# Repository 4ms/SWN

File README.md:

# Spherical Wavetable Navigator

Firmware for the Spherical Wavetable Navigator, a Eurorack-format module from 4ms Company.

## Setting up the gcc-arm toolchain
You need to install the GCC ARM toolchain.
This project is known to compile with arm-none-eabi-gcc version 8.2.1 (8-2019q4) and 7.3.1 (7-2018q2).

If you're new to embedded development and not comfortable on the command line, you may wish to install an IDE. ST has an official IDE based on Eclipse called [STM32CubeIDE](https://www.st.com/en/development-tools/stm32cubeide.html). Or you can roll-your-own Eclipse using [GCC ARM with Eclipse](https://gnu-mcu-eclipse.github.io/). There are also commerical software packages which can be easily found by searching.

Another option is to use a fully-featured text editor such as VSCode or Sublime Text. You can configure these to run commands to compile and flash/program your project onto your SWN, too. There are ARM debugging extensions available, too. On the other hand, if you're happiest using the command line and prefer to write code with vim, emacs, etc, you can also do everything without having to lift your hand from the keyboard except to twiddle knobs on the SWN.

### Using the Virtual Machine ###

4ms has a virtual machine that provides a consistant development environment for compiling. Check out this project and follow the instructions in its README: [4ms-dev-env](https://github.com/4ms/4ms-dev-env). The SWN repo comes pre-cloned when you start this virtual machine.

First, follow the instructions on [vagrant's site](https://www.vagrantup.com/intro/getting-started) to install vagrant and VirtualBox.

Then, building the SWN project is as simple as this:

```
git clone https://github.com/4ms/4ms-dev-env.git
cd 4ms-dev-env
vagrant up
vagrant ssh
cd SWN
make
```

At present, the 4ms-dev-env is only setup to compile, not to flash (program), or debug.
If you decide to use the virtual machine to compile, you'll still need to use your local system to program the compiled code onto SWN. Skip down to the **Programmer** section.

### Mac OSX using Brew ###

For Mac OSX, you can use brew to install the gcc-arm toolchain.
First, install brew if you haven't already:
```
ruby -e "$(curl -fsSL https://raw.githubusercontent.com/Homebrew/install/master/install)"
```

Then, install the gcc-arm toolchain v7.3.1:

```
brew tap nitsky/stm32
brew install arm-none-eabi-gcc
```

Continue below to **Clone the Projects**

Alternatively, you can follow the _Linux orMac OSX_ instructions below to get v8.2.1.

### Linux or Mac OSX ###

For Linux or Mac OSX, download GNU ARM Embedded Toolchain version 8-2018-q4-major from [Launchpad](https://launchpad.net/gcc-arm-embedded/+download).

Direct links: [Mac OSX gcc-arm 8.2.1](https://developer.arm.com/-/media/Files/downloads/gnu-rm/8-2018q4/gcc-arm-none-eabi-8-2018-q4-major-mac.tar.bz2) ... [Linux gcc-arm 8.2.1](https://developer.arm.com/-/media/Files/downloads/gnu-rm/8-2018q4/gcc-arm-none-eabi-8-2018-q4-major-linux.tar.bz2).

Then unzip them: Double-clicking them on MacOS might work, or type this:

```
cd ~/Downloads ##whatever your download directory is
tar jxf gcc-arm-none-eabi-8-2018-q4-major-*.tar.bz2
```

Next, move the unzipped directory to somewhere sensible and add the `bin/` dir to your PATH:

```
mv gcc-arm-none-eabi-8-2018-q4-major $HOME/myprojectdir
echo "export PATH=$HOME/myprojectdir/gcc-arm-none-eabi-8-2018-q4-major/bin:\$PATH" >> $HOME/.bash_profile
source $HOME/.bash_profile

```

Of course, modify the above with the actual directory you want to put the toolchain, and your shell start-up script if you're using zsh or something else.

Continue below to **Clone the Projects**

### Windows
Download the GNU ARM Embedded Toolchain version 8-2018-q4-major from [Launchpad](https://launchpad.net/gcc-arm-embedded/+download). Download the Installer for your Windows verion (don't download the .zip file, download the .exe file).

Run the installer, and continue below.

## Clone the Project ##

If you are using the virtual machine, this will already be cloned for you, so skip ahead.

Make sure git is installed on your system. (OSX: type "brew install git" into the Terminal).

Create a work directory, and enter it:
 
	mkdir myhackdir && cd myhackdir

Clone the SWN repository:

	git clone https://github.com/4ms/SWN.git  
	cd SWN

## Compiling ##
Make your changes to the code in the SWN directory. When ready to compile, make the project like this:

	make
	
This creates an main.elf, main.bin, and main.hex file in the build/ directory. See the Programmer section below for how to get these files onto your SWN.

## Programmer (Hardware) ##

Once you compile your firmware, you need to flash it to your SWN. You will need a hardware device that connects to your computer's USB port. The other side of the programmer has a header that conencts to the SWN's 4-pin SWD header.

You have several options:

### Option 1) ST-LINKv2 programmer ###

The [ST-LINK v2 from ST corporation](http://www.mouser.com/search/ProductDetail.aspx?R=0virtualkey0virtualkeyST-LINK-V2) is the offical programmer from ST (who makes the chip that needs programming). The ST-LINK v2 has a 20-pin JTAG header, and you need to connect four of these to your SWN. More details on this are below.

The ST-LINKv2 programmer can be used with ST-LINK software for Mac, Linux, or Windows; or ST-UTIL software for Windows; or STM32CubeProgrammer software for any platform. 

### Option 2) Discovery board programmer ###

The [STM32 Discovery boards](http://www.mouser.com/search/ProductDetail.aspx?R=0virtualkey0virtualkeySTM32F407G-DISC1) are low-cost (around US$25) and work great as a programmer and debugger. The 'Disco' board is essentially an ST-LINKv2, plus some extra stuff. While the ST-LINK v2 is encased in a plastic enclosure, the Discovery board is open and could potentially be damaged if you're not careful. Read the Discovery board's manual to learn about setting the jumpers to use it as an SWD programmer (rather than an evaluation board). ST makes many variations of the Discovery board, and to my knowledge they all contain an ST-LINK programmer.

The Discovery board programmer is essentially an ST-LINKv2, so it can be used with all the same software that the ST-LINKv2 can (see above section).

### Option 3) SEGGER's J-Link or J-Trace ###

Another option is [SEGGER's J-link programmer](https://www.segger.com/jlink-debug-probes.html). There is an educational version which is very affordable and a good choice for a programmer if you meet the requirements for education use. There are various professional commercial versions with a number of useful features. The J-link uses SEGGER's propriety software, Ozone, which not only will flash a hex or bin file, but can be used as a powerful GUI debugger if you use it to open the .elf file. There also are command-line commands for flashing.
J-Link software runs on Mac, Linux, and Windows.

### Option 4) Audio Bootloader ###

The SWN has an audio bootloader built-in, so you can just compile your project using `make wav` and then play the wav file into the audio input of the SWN while in bootloader mode (see SWN User Manual for detailed procedure). No additional hardware or software is necessary.

This works well and is the safest option. However it's very slow (up to 5 minutes per update, or 11+ minutes if you include all new factory wavetables). If you are going to be making a series of changes, this will be a very slow process!

When ready to build an audio file for the bootloader, make it like this:

	make wav

This requires python to run. It creates the file `main.wav` in the `build/` directory. Play the file from a computer or device into the SWN by following the instructions in the User Manual on the [4ms SWN page](http://4mscompany.com/SWN). 

## Programmer (Software)

Depending on the hardware you chose, one or more of the following software options will work:

### ST-LINK ###

This software works with the ST-LINK v2 and the Discovery board to flash your SWN.

__MacOS:__

```
brew install stlink
```

__Linux:__

Use your package manager to install `stlink-tools`. See [stlink README](https://github.com/stlink-org/stlink) for direct links.

__Windows:__

Download the [latest binary (v1.3.0)](https://github.com/stlink-org/stlink/releases/download/v1.3.0/stlink-1.3.0-win64.zip). If that link doesn't work anymore, or you want to try a newer version, go to [stlink-org/stlink github page](https://github.com/stlink-org/stlink).

__Programming using st-link__

You can flash the compiled .bin file by typing:

	st-flash write build/main.bin 0x08010000
	
This writes the main.bin file starting at the 0x08010000 sector, which is the first sector of the application code.

__Debugging__

The gcc-arm toolchain includes a gdb debugger, but you'll need a server to use it. The st-link software includes st-util which will provide this. OpenOCD and J-link are two other options. Configuring debugging is beyond the scope of this README, but there are plenty of tutorials online. See the [stlink README](https://github.com/stlink-org/stlink) for a quick start.

### J-Link/Ozone ###

If you're using a J-Link or J-Trace hardware programmer to flash your SWN, download and install [Ozone](https://www.segger.com/downloads/jlink). Ozone is a GUI debugger which can program, too. For command-line options, consider [J-Link Software and Documentation Pack](https://www.segger.com/j-link-software.html), which contains the GDB server and other tools.

To program your SWN, open Ozone and then use the Project Wizard to create a new project. Select the STM32F765ZG for the chip. Use the default settings elsewhere. On the page that lets you select a file, select the main.elf file that you compiled. You can then save this project. To program, just click the green power/arrow symbol at the upper left.

You also can use the CLI tools to flash the hex/elf file, see J-Link documentation for details.

J-Link and Ozone is available for Mac, Windows, and Linux.

### STM32CubeProgrammer ###

The STM32CubeProgrammer is ST's official programaming software available for all platforms. [You can find it here](https://www.st.com/en/development-tools/stm32cubeprog.html)

Documentation is included with the download.

### ST-UTIL (Windows only) ###

ST-UTIL is a program from ST that runs on Windows only. You can find it on [ST.com](https://my.st.com/content/my_st_com/en/products/development-tools/software-development-tools/stm32-software-development-tools/stm32-programmers/stsw-link004.html)

It works with the ST-LINKv2 and Discovery boards.

## Connecting the programmer to the SWN ##

**Discovery Board**: The Discovery board has a 6-pin SWD header, and you can connect that pin-for-pin to the first 4 pins on the SWN's SWD header. You can use a 0.1" spaced 4-pin Jumper Wire such as [this one from Sparkfun](https://www.sparkfun.com/products/10364). Pay attention to Pin 1 (marked by "1" on the SWN board), or you risk damaging the ARM chip.

**ST-LINK v2 or SEGGER J-Link**: Both the ST-LINK and the SEGGER J-link have a 20-pin JTAG connector. You need to connect 4 of these pins to the SWN's 4-pin SWD connector, using 4 wires: [here's a pack of 10](https://www.sparkfun.com/products/8430). Pay attention to Pin 1 (marked by "1" on the SWN board), or you risk damaging the ARM chip.
 
Look at these images:
 
  * JTAG: [20-pin pinout](http://www.jtagtest.com/pinouts/arm20)
  * SWD: [6-pin pinout](https://wiki.paparazziuav.org/wiki/File:Swd_header_discovery_board.png)
  * JTAG-to-SWD: [JTAG-to-SWD-pinout](https://4mscompany.com/JTAG-to-SWD-pinout.png). 

Then use your jumper wires to connect:
 
  * SWD pin 1 (VDD) -> JTAG pin 1 (VREF)
  * SWD pin 2 (SWCLK) -> JTAG pin 9 (TCK)
  * SWD pin 3 (GND) -> JTAG pin 4 (GND)
  * SWD pin 4 (SWDIO) -> JTAG pin 7 (TMS)

Here's more info in case you want it explained in another way:

  * [This image](https://www.alexwhittemore.com/wp-content/uploads/2014/08/schematic.jpg) draws this out. (Taken from [this post](https://www.alexwhittemore.com/st-linkv2-swd-jtag-adapter/))
  * [ST's manual](http://www.st.com/content/ccc/resource/technical/document/user_manual/70/fe/4a/3f/e7/e1/4f/7d/DM00039084.pdf/files/DM00039084.pdf/jcr:content/translations/en.DM00039084.pdf)
  * [How to make an adaptor](http://gnuarmeclipse.github.io/developer/j-link-stm32-boards/#the-st-6-pin-swd-connector)
  * Make your own adaptor from these gerber files: [JTAG-SWD-adaptor](https://github.com/4ms/pcb-JTAG-SWD-adaptor).

## Bootloader Information ##

The bootloader is in a folder called `bootloader/`.
It's based on the stm-audio-bootloader from [pichenettes](https://github.com/pichenettes/eurorack). 

The bootloader is already installed on all factory-built SWN, so you don't need to mess with this project if you're just planning on modifying your SWN code. The bootloader allows you to replace the firmware by playing a compiled audio file into the Waveform In jack.

Doing `make` from within the `bootloader/` directory will build the bootloader and also use the main SWN app's `main.hex` file to create a combined hex file. This file is a complete flash dump of a factory SWN. After building the SWN first, and then the bootloader, the file will be in `SWN/bootloader/build/bootloader-app-combo/`. There is a hex and a bin version in that folder.

__Oops, I overwrote the bootloader and now it won't boot...__

The bootloader lives at 0x08000000, so if you overwrite that sector you will overwrite the bootloader. And then it won't boot. The best way is to re-flash the bootloader. Do this:

	st-flash write bootloader/build/bootloader-app-combo/SWN_combo.bin 0x08000000
	
Or if the combo is not working, you could try just the bootloader:

	st-flash write bootloader/build/bootloader/bootloader.bin 0x08000000

## License ##

The code (software) is licensed by the MIT license.

The hardware is licensed by the [CC BY-NC-SA license](https://creativecommons.org/licenses/by-nc-sa/4.0/) (Creative Commons, Attribution, NonCommercial, ShareAlike).

See LICENSE file.

I would like to see others build and modify the SWN and SWN-influenced works, in a non-commercial manner. My intent is not to limit the educational use nor to prevent people buying hardware components/PCBs collectively in a group. If you have any questions regarding the license or appropriate use, please do not hesitate to contact me! 

## Guidelines for derivative works ##

Do not include the text "4ms" or "4ms Company" or the graphic 4ms logo on any derivative works. This includes faceplates, enclosures, PCBs, and front-panels. It's OK (but not required) to include the text "Spherical Wavetable Navigator" or "SWN" if you wish.

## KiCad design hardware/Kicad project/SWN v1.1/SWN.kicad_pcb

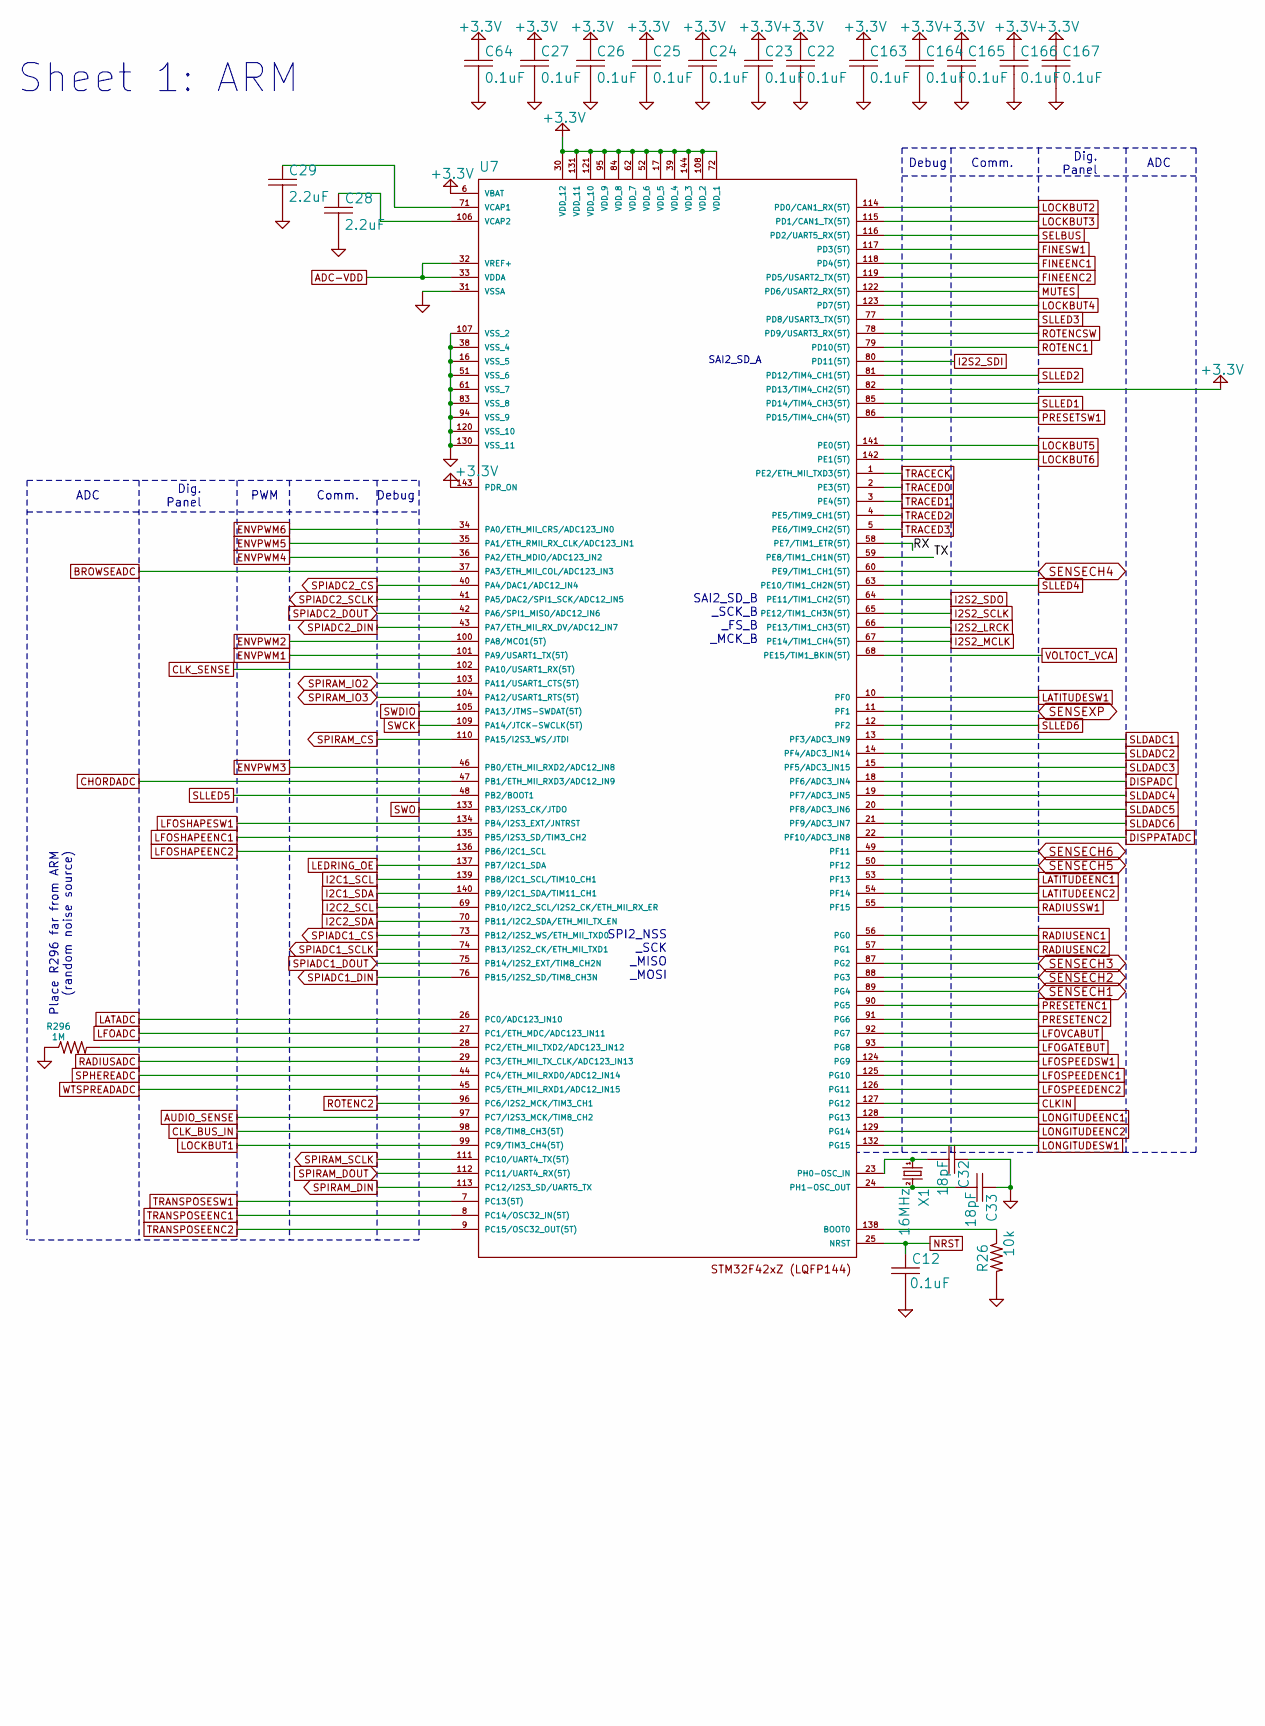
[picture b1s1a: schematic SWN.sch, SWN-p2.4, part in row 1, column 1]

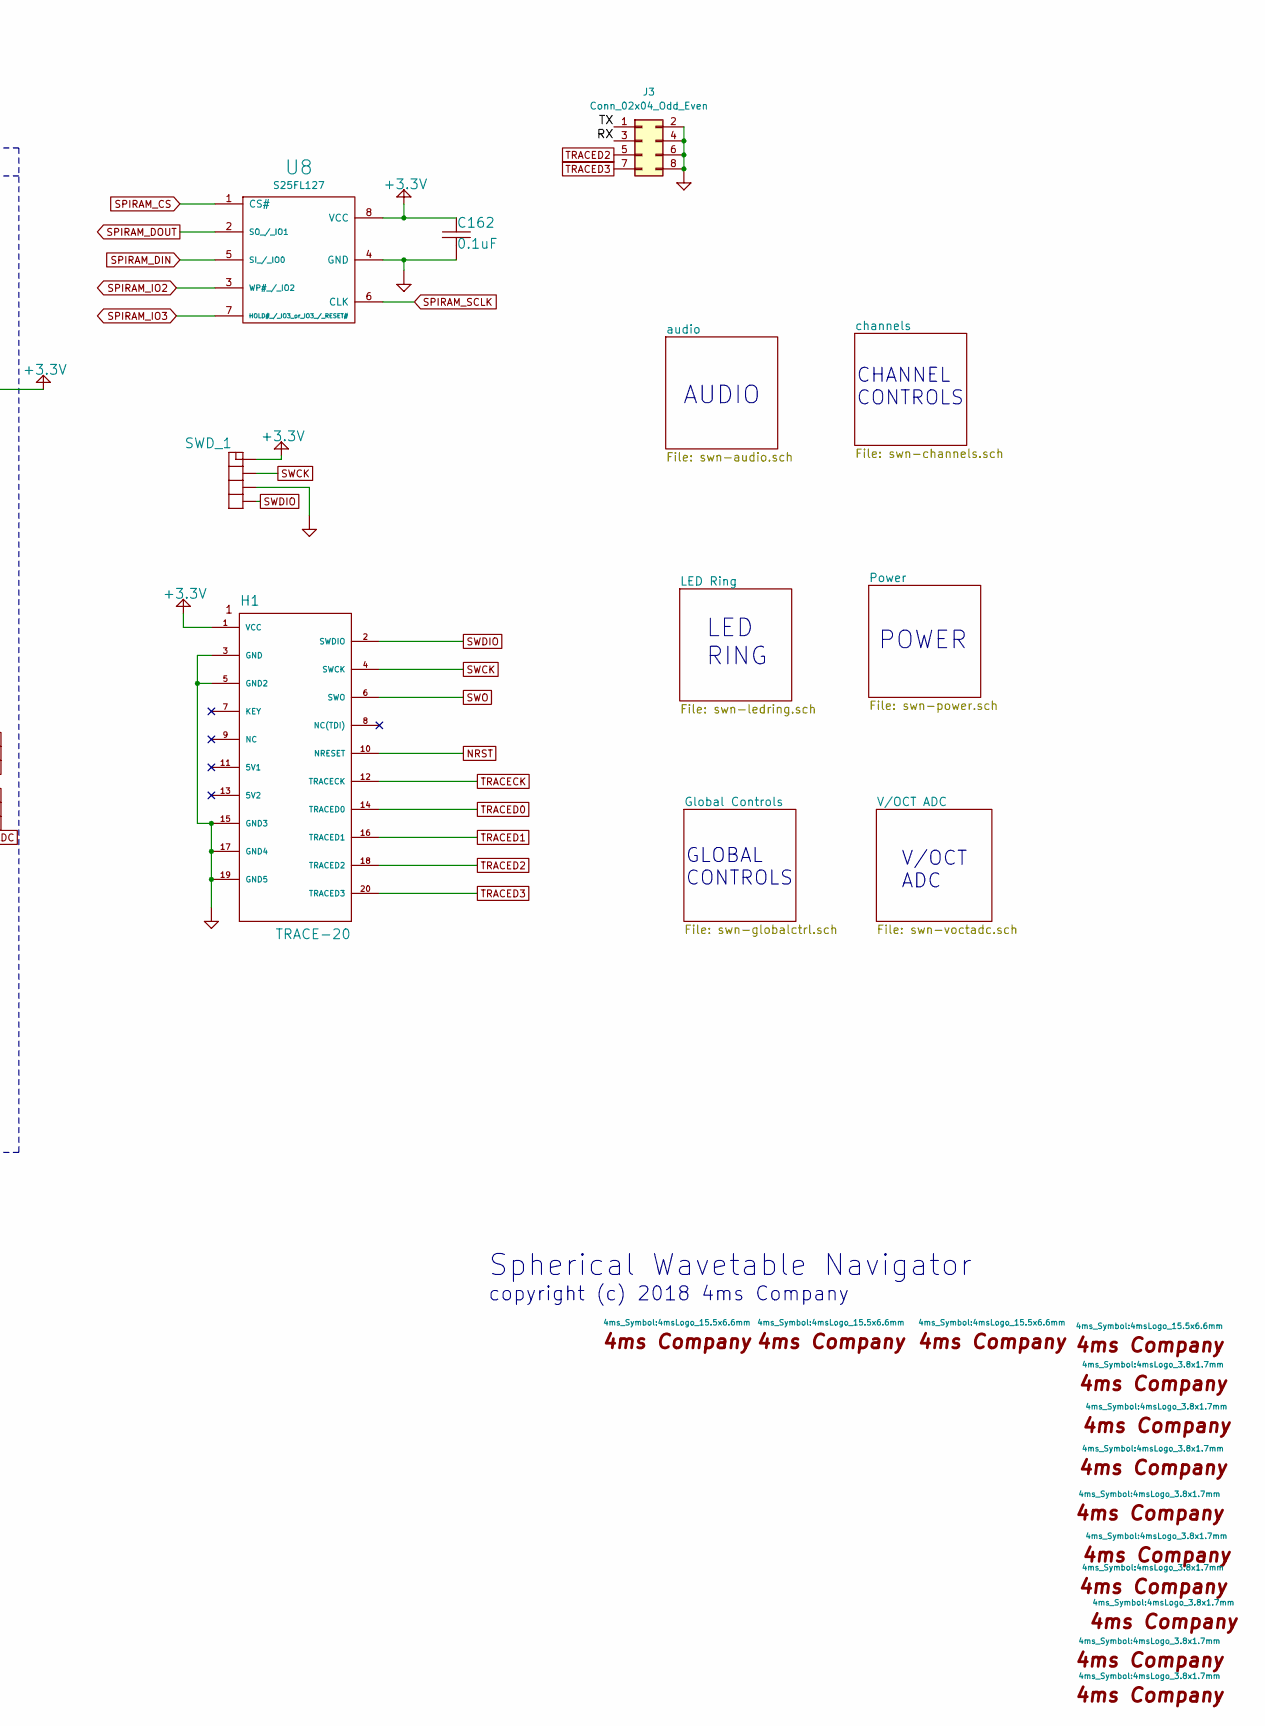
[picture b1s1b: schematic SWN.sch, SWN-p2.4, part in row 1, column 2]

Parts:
C12, C22, C23, C24, C25, C26, C27, C64, C162, C163, C164, C165, C166, C167: 0.1uF; C0603
C28, C29: 2.2uF; C0603
C32, C33: 18pF; C0603
G***1, G***2, G***3, G***4: 4ms-logo; 4msLogo_15.5x6.6mm
G***5, G***6, G***7, G***8, G***9, G***10, G***11, G***12, G***13: 4ms-logo; 4msLogo_3.8x1.7mm
H1: TRACE-20; CONN-2x10-SMT-127
J3: Conn_02x04_Odd_Even; Pins_2x04_2.54mm_TH
R26: 10k; R0603
R296: 1M; R0603
SWD_1: HEADER-1X4; Pins_1x04_2.54mm_TH_SWD
U7: STM32F765ZG; LQFP-144_ARM_20x20mm_Pitch0.5mm
U8: S25FL127; SOIC-8_5.28x4.9mm_Pitch1.27mm
X1: 16MHz; FA-238-Pins1and2diag

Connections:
+3.3V: C22.1, C23.1, C24.1, C25.1, C26.1, C27.1, C64.1, C162.1, C163.1, C164.1, C165.1, C166.1, C167.1, H1.1 (VCC), SWD_1.1, U7.6 (VBAT), U7.17 (VDD_5), U7.30 (VDD_12), U7.39 (VDD_4), U7.52 (VDD_6), U7.62 (VDD_7), U7.72 (VDD_1), U7.82 (PD13/TIM4_CH2(5T)), U7.84 (VDD_8), U7.95 (VDD_9), U7.108 (VDD_2), U7.121 (VDD_10), U7.131 (VDD_11), U7.143 (PDR_ON), U7.144 (VDD_3), U8.8 (VCC); also elsewhere on the board
/RX: J3.3, U7.58 (PE7/TIM1_ETR(5T))
/TX: J3.1, U7.59 (PE8/TIM1_CH1N(5T))
ADC-VDD: U7.32 (VREF+), U7.33 (VDDA); also elsewhere on the board
AUDIO_SENSE: U7.97 (PC7/I2S3_MCK/TIM8_CH2); also elsewhere on the board
BROWSEADC: U7.37 (PA3/ETH_MII_COL/ADC123_IN3); also elsewhere on the board
CHORDADC: U7.47 (PB1/ETH_MII_RXD3/ADC12_IN9); also elsewhere on the board
CLKIN: U7.127 (PG12); also elsewhere on the board
CLK_BUS_IN: U7.98 (PC8/TIM8_CH3(5T)); also elsewhere on the board
CLK_SENSE: U7.102 (PA10/USART1_RX(5T)); also elsewhere on the board
DISPADC: U7.18 (PF6/ADC3_IN4); also elsewhere on the board
DISPPATADC: U7.22 (PF10/ADC3_IN8); also elsewhere on the board
ENVPWM1: U7.101 (PA9/USART1_TX(5T)); also elsewhere on the board
ENVPWM2: U7.100 (PA8/MCO1(5T)); also elsewhere on the board
ENVPWM3: U7.46 (PB0/ETH_MII_RXD2/ADC12_IN8); also elsewhere on the board
ENVPWM4: U7.36 (PA2/ETH_MDIO/ADC123_IN2); also elsewhere on the board
ENVPWM5: U7.35 (PA1/ETH_RMII_RX_CLK/ADC123_IN1); also elsewhere on the board
ENVPWM6: U7.34 (PA0/ETH_MII_CRS/ADC123_IN0); also elsewhere on the board
FINEENC1: U7.118 (PD4(5T)); also elsewhere on the board
FINEENC2: U7.119 (PD5/USART2_TX(5T)); also elsewhere on the board
FINESW1: U7.117 (PD3(5T)); also elsewhere on the board
I2C1_SCL: U7.139 (PB8/I2C1_SCL/TIM10_CH1); also elsewhere on the board
I2C1_SDA: U7.140 (PB9/I2C1_SDA/TIM11_CH1); also elsewhere on the board
I2C2_SCL: U7.69 (PB10/I2C2_SCL/I2S2_CK/ETH_MII_RX_ER); also elsewhere on the board
I2C2_SDA: U7.70 (PB11/I2C2_SDA/ETH_MII_TX_EN); also elsewhere on the board
I2S2_LRCK: U7.66 (PE13/TIM1_CH3(5T)); also elsewhere on the board
I2S2_MCLK: U7.67 (PE14/TIM1_CH4(5T)); also elsewhere on the board
I2S2_SCLK: U7.65 (PE12/TIM1_CH3N(5T)); also elsewhere on the board
I2S2_SDI: U7.80 (PD11(5T)); also elsewhere on the board
I2S2_SDO: U7.64 (PE11/TIM1_CH2(5T)); also elsewhere on the board
LATADC: U7.26 (PC0/ADC123_IN10); also elsewhere on the board
LATITUDEENC1: U7.53 (PF13); also elsewhere on the board
LATITUDEENC2: U7.54 (PF14); also elsewhere on the board
LATITUDESW1: U7.10 (PF0); also elsewhere on the board
LEDRING_OE: U7.137 (PB7/I2C1_SDA); also elsewhere on the board
LFOADC: U7.27 (PC1/ETH_MDC/ADC123_IN11); also elsewhere on the board
LFOGATEBUT: U7.93 (PG8); also elsewhere on the board
LFOSHAPEENC1: U7.135 (PB5/I2S3_SD/TIM3_CH2); also elsewhere on the board
LFOSHAPEENC2: U7.136 (PB6/I2C1_SCL); also elsewhere on the board
LFOSHAPESW1: U7.134 (PB4/I2S3_EXT/JNTRST); also elsewhere on the board
LFOSPEEDENC1: U7.125 (PG10); also elsewhere on the board
LFOSPEEDENC2: U7.126 (PG11); also elsewhere on the board
LFOSPEEDSW1: U7.124 (PG9); also elsewhere on the board
LFOVCABUT: U7.92 (PG7); also elsewhere on the board
LOCKBUT1: U7.99 (PC9/TIM3_CH4(5T)); also elsewhere on the board
LOCKBUT2: U7.114 (PD0/CAN1_RX(5T)); also elsewhere on the board
LOCKBUT3: U7.115 (PD1/CAN1_TX(5T)); also elsewhere on the board
LOCKBUT4: U7.123 (PD7(5T)); also elsewhere on the board
LOCKBUT5: U7.141 (PE0(5T)); also elsewhere on the board
LOCKBUT6: U7.142 (PE1(5T)); also elsewhere on the board
LONGITUDEENC1: U7.128 (PG13); also elsewhere on the board
LONGITUDEENC2: U7.129 (PG14); also elsewhere on the board
LONGITUDESW1: U7.132 (PG15); also elsewhere on the board
MUTES: U7.122 (PD6/USART2_RX(5T)); also elsewhere on the board
NRST: C12.1, H1.10 (NRESET), U7.25 (NRST)
unnamed: C28.1, U7.106 (VCAP2)
unnamed: C29.1, U7.71 (VCAP1)
unnamed: C32.2, U7.23 (PH0-OSC_IN), X1.1
unnamed: C33.2, U7.24 (PH1-OSC_OUT), X1.2
unnamed: R26.1, U7.138 (BOOT0)
unnamed: R296.2, U7.28 (PC2/ETH_MII_TXD2/ADC123_IN12)
PRESETENC1: U7.90 (PG5); also elsewhere on the board
PRESETENC2: U7.91 (PG6); also elsewhere on the board
PRESETSW1: U7.86 (PD15/TIM4_CH4(5T)); also elsewhere on the board
RADIUSADC: U7.29 (PC3/ETH_MII_TX_CLK/ADC123_IN13); also elsewhere on the board
RADIUSENC1: U7.56 (PG0); also elsewhere on the board
RADIUSENC2: U7.57 (PG1); also elsewhere on the board
RADIUSSW1: U7.55 (PF15); also elsewhere on the board
ROTENC1: U7.79 (PD10(5T)); also elsewhere on the board
ROTENC2: U7.96 (PC6/I2S2_MCK/TIM3_CH1); also elsewhere on the board
ROTENCSW: U7.78 (PD9/USART3_RX(5T)); also elsewhere on the board
SELBUS: U7.116 (PD2/UART5_RX(5T)); also elsewhere on the board
SENSECH1: U7.89 (PG4); also elsewhere on the board
SENSECH2: U7.88 (PG3); also elsewhere on the board
SENSECH3: U7.87 (PG2); also elsewhere on the board
SENSECH4: U7.60 (PE9/TIM1_CH1(5T)); also elsewhere on the board
SENSECH5: U7.50 (PF12); also elsewhere on the board
SENSECH6: U7.49 (PF11); also elsewhere on the board
SENSEXP: U7.11 (PF1); also elsewhere on the board
SLDADC1: U7.13 (PF3/ADC3_IN9); also elsewhere on the board
SLDADC2: U7.14 (PF4/ADC3_IN14); also elsewhere on the board
SLDADC3: U7.15 (PF5/ADC3_IN15); also elsewhere on the board
SLDADC4: U7.19 (PF7/ADC3_IN5); also elsewhere on the board
SLDADC5: U7.20 (PF8/ADC3_IN6); also elsewhere on the board
SLDADC6: U7.21 (PF9/ADC3_IN7); also elsewhere on the board
SLLED1: U7.85 (PD14/TIM4_CH3(5T)); also elsewhere on the board
SLLED2: U7.81 (PD12/TIM4_CH1(5T)); also elsewhere on the board
SLLED3: U7.77 (PD8/USART3_TX(5T)); also elsewhere on the board
SLLED4: U7.63 (PE10/TIM1_CH2N(5T)); also elsewhere on the board
SLLED5: U7.48 (PB2/BOOT1); also elsewhere on the board
SLLED6: U7.12 (PF2); also elsewhere on the board
SPHEREADC: U7.44 (PC4/ETH_MII_RXD0/ADC12_IN14); also elsewhere on the board
SPIADC1_CS: U7.73 (PB12/I2S2_WS/ETH_MII_TXD0); also elsewhere on the board
SPIADC1_DIN: U7.76 (PB15/I2S2_SD/TIM8_CH3N); also elsewhere on the board
SPIADC1_DOUT: U7.75 (PB14/I2S2_EXT/TIM8_CH2N); also elsewhere on the board
SPIADC1_SCLK: U7.74 (PB13/I2S2_CK/ETH_MII_TXD1); also elsewhere on the board
SPIADC2_CS: U7.40 (PA4/DAC1/ADC12_IN4); also elsewhere on the board
SPIADC2_DIN: U7.43 (PA7/ETH_MII_RX_DV/ADC12_IN7); also elsewhere on the board
SPIADC2_DOUT: U7.42 (PA6/SPI1_MISO/ADC12_IN6); also elsewhere on the board
SPIADC2_SCLK: U7.41 (PA5/DAC2/SPI1_SCK/ADC12_IN5); also elsewhere on the board
SPIRAM_CS: U7.110 (PA15/I2S3_WS/JTDI), U8.1 (CS#)
SPIRAM_DIN: U7.113 (PC12/I2S3_SD/UART5_TX), U8.5 (SI_/_IO0)
SPIRAM_DOUT: U7.112 (PC11/UART4_RX(5T)), U8.2 (SO_/_IO1)
SPIRAM_IO2: U7.103 (PA11/USART1_CTS(5T)), U8.3 (WP#_/_IO2)
SPIRAM_IO3: U7.104 (PA12/USART1_RTS(5T)), U8.7 (HOLD#_/_IO3_or_IO3_/_RESET#)
SPIRAM_SCLK: U7.111 (PC10/UART4_TX(5T)), U8.6 (CLK)
SWCK: H1.4 (SWCK), SWD_1.2, U7.109 (PA14/JTCK-SWCLK(5T))
SWDIO: H1.2 (SWDIO), SWD_1.4, U7.105 (PA13/JTMS-SWDAT(5T))
SWO: H1.6 (SWO), U7.133 (PB3/I2S3_CK/JTDO)
TRACECK: H1.12 (TRACECK), U7.1 (PE2/ETH_MII_TXD3(5T))
TRACED0: H1.14 (TRACED0), U7.2 (PE3(5T))
TRACED1: H1.16 (TRACED1), U7.3 (PE4(5T))
TRACED2: H1.18 (TRACED2), J3.5, U7.4 (PE5/TIM9_CH1(5T))
TRACED3: H1.20 (TRACED3), J3.7, U7.5 (PE6/TIM9_CH2(5T))
TRANSPOSEENC1: U7.8 (PC14/OSC32_IN(5T)); also elsewhere on the board
TRANSPOSEENC2: U7.9 (PC15/OSC32_OUT(5T)); also elsewhere on the board
TRANSPOSESW1: U7.7 (PC13(5T)); also elsewhere on the board
VOLTOCT_VCA: U7.68 (PE15/TIM1_BKIN(5T)); also elsewhere on the board
WTSPREADADC: U7.45 (PC5/ETH_MII_RXD1/ADC12_IN15); also elsewhere on the board

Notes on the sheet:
Spherical Wavetable Navigator
copyright (c) 2018 4ms Company
Sheet 1: ARM
AUDIO
CHANNEL CONTROLS
GLOBAL CONTROLS
LED RING
POWER
V/OCT ADC
Place R296 far from ARM (random noise source)
ADC
Dig. Panel
PWM
Comm.
Debug
SAI2_SD_A
SAI2_SD_B _SCK_B _FS_B _MCK_B
SPI2_NSS _SCK _MISO _MOSI

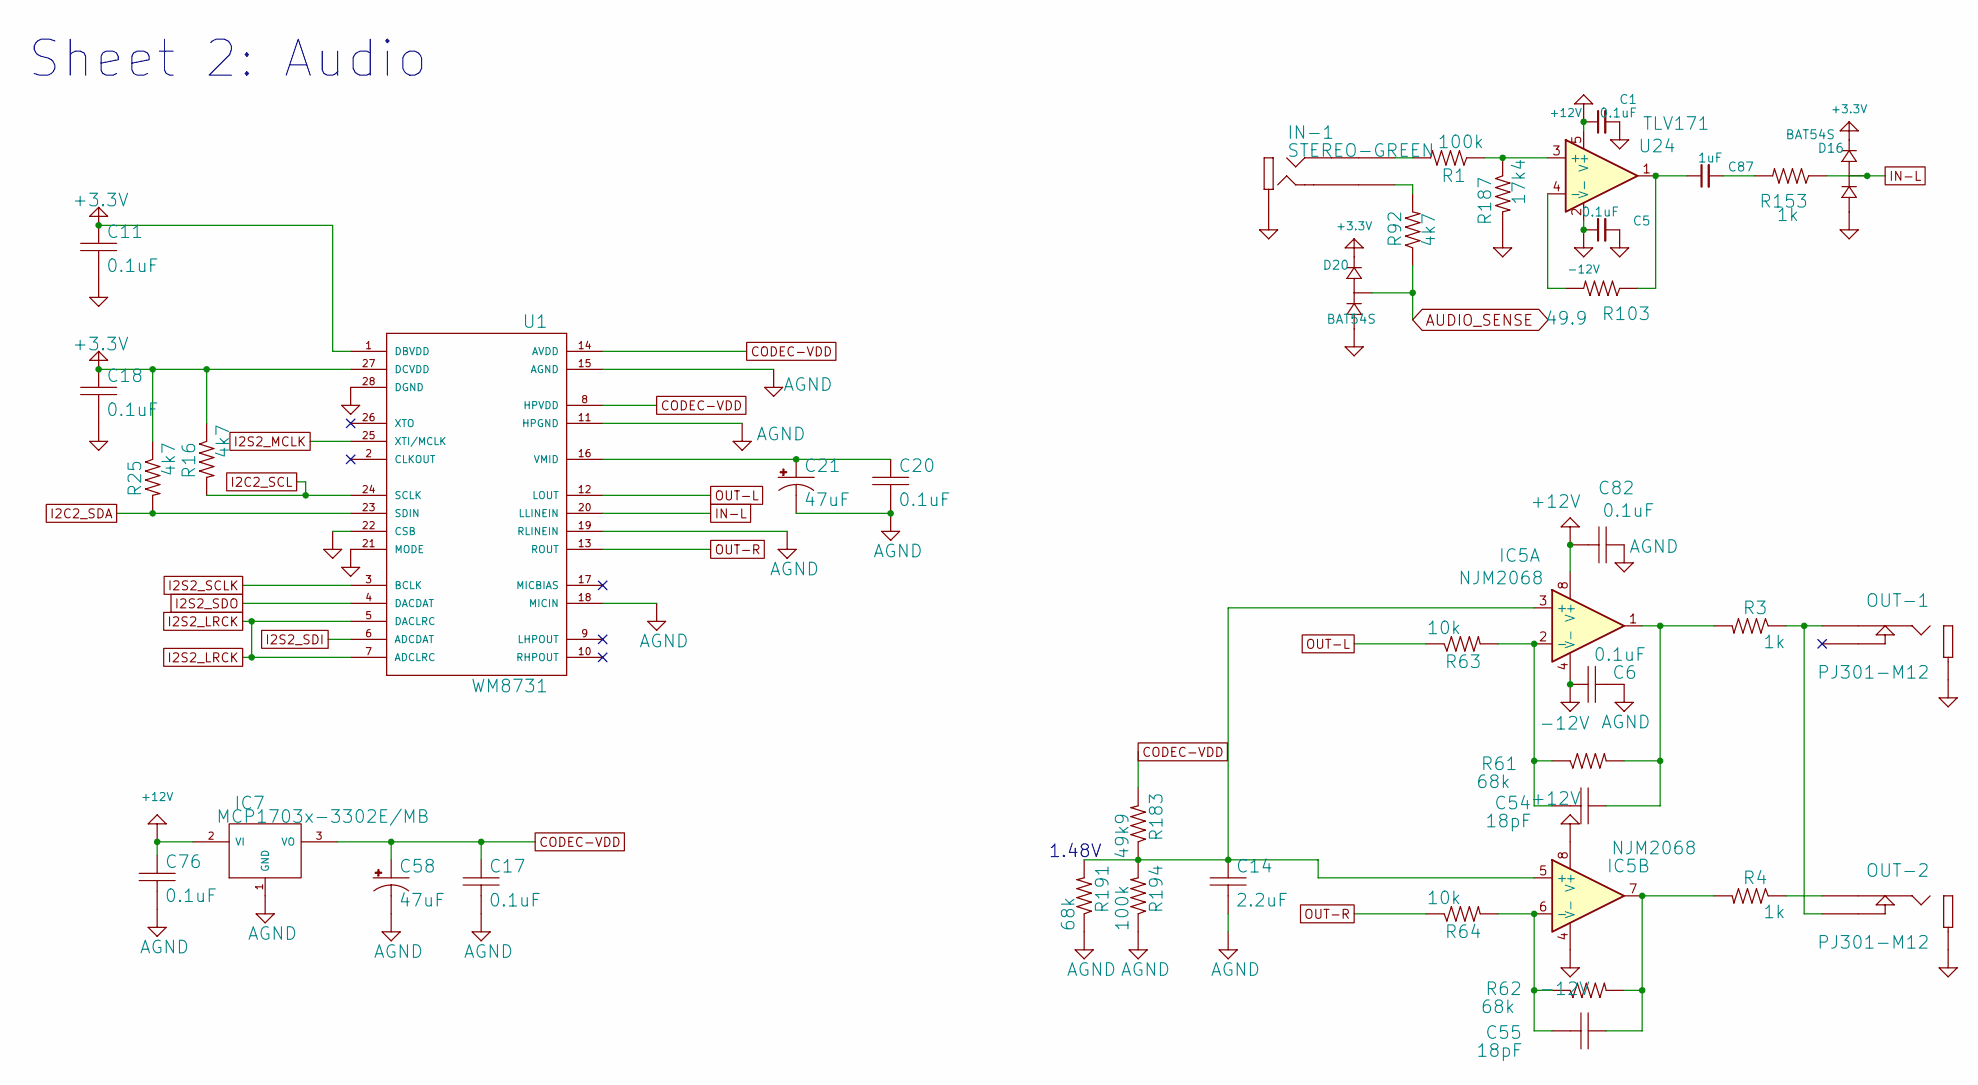
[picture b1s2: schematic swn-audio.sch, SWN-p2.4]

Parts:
C1, C5, C6, C11, C17, C18, C20, C76, C82: 0.1uF; C0603
C14: 2.2uF; C0603
C21, C58: 47uF; CP_Elec_5x5.3
C54, C55: 18pF; C0603
C87: 1uF; C0603
D16, D20: BAT54S; SOT23
IC5: NJM2068; TSSOP-8_4.4x3mm_Pitch0.65mm
IC7: MCP1703x-3302E/MB; SOT-89-3
IN-1: STEREO-GREEN; PJ301M-12
OUT-1, OUT-2: PJ301-M12; PJ301M-12
R1, R194: 100k; R0603
R3, R4, R153: 1k; R0603
R16, R25, R92: 4k7; R0603
R61, R62, R191: 68k; R0603
R63, R64: 10k; R0603
R103: 49.9; R0603
R183: 49k9; R0603
R187: 17k4; R0603
U1: WM8731; SSOP-28
U24: TLV171; SOT-23-5

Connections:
+3.3V: C11.1, C18.1, D16.2 (CATHODE), D20.2 (CATHODE), R16.1, R25.1, U1.1 (DBVDD), U1.27 (DCVDD); also elsewhere on the board
+12V: C1.1, C76.1, C82.2, IC5.8 (V+), IC7.2 (VI), U24.5 (V+); also elsewhere on the board
-12V: C5.1, C6.1, IC5.4 (V-), U24.2 (V-); also elsewhere on the board
AGND: C6.2, C14.2, C17.2, C20.2, C21.2 (-), C58.2 (-), C76.2, C82.1, IC7.1 (GND), R191.1, R194.1, U1.11 (HPGND), U1.15 (AGND), U1.18 (MICIN), U1.19 (RLINEIN); also elsewhere on the board
AUDIO_SENSE: D20.3 (COMMON), R92.1; also elsewhere on the board
CODEC-VDD: C17.1, C58.1 (+), IC7.3 (VO), R183.2, U1.8 (HPVDD), U1.14 (AVDD)
I2C2_SCL: R16.2, U1.24 (SCLK); also elsewhere on the board
I2C2_SDA: R25.2, U1.23 (SDIN); also elsewhere on the board
I2S2_LRCK: U1.5 (DACLRC), U1.7 (ADCLRC); also elsewhere on the board
I2S2_MCLK: U1.25 (XTI/MCLK); also elsewhere on the board
I2S2_SCLK: U1.3 (BCLK); also elsewhere on the board
I2S2_SDI: U1.6 (ADCDAT); also elsewhere on the board
I2S2_SDO: U1.4 (DACDAT); also elsewhere on the board
IN-L: D16.3 (COMMON), R153.1, U1.20 (LLINEIN)
unnamed: C14.1, IC5.3 (+), IC5.5 (+), R183.1, R191.2, R194.2
unnamed: C20.1, C21.1 (+), U1.16 (VMID)
unnamed: C54.1, IC5.1, R3.2, R61.2
unnamed: C54.2, IC5.2 (-), R61.1, R63.2
unnamed: C55.1, IC5.7, R4.2, R62.2
unnamed: C55.2, IC5.6 (-), R62.1, R64.2
unnamed: C87.1, R103.1, U24.1
unnamed: C87.2, R153.2
unnamed: IN-1.1 (TIP), R1.2
unnamed: IN-1.3 (TIP-SW), R92.2
unnamed: OUT-1.1 (TIP), OUT-2.3 (TIP-SW), R3.1
unnamed: OUT-2.1 (TIP), R4.1
unnamed: R1.1, R187.1, U24.3 (+)
unnamed: R103.2, U24.4 (-)
OUT-L: R63.1, U1.12 (LOUT)
OUT-R: R64.1, U1.13 (ROUT)

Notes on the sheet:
1.48V
Sheet 2: Audio

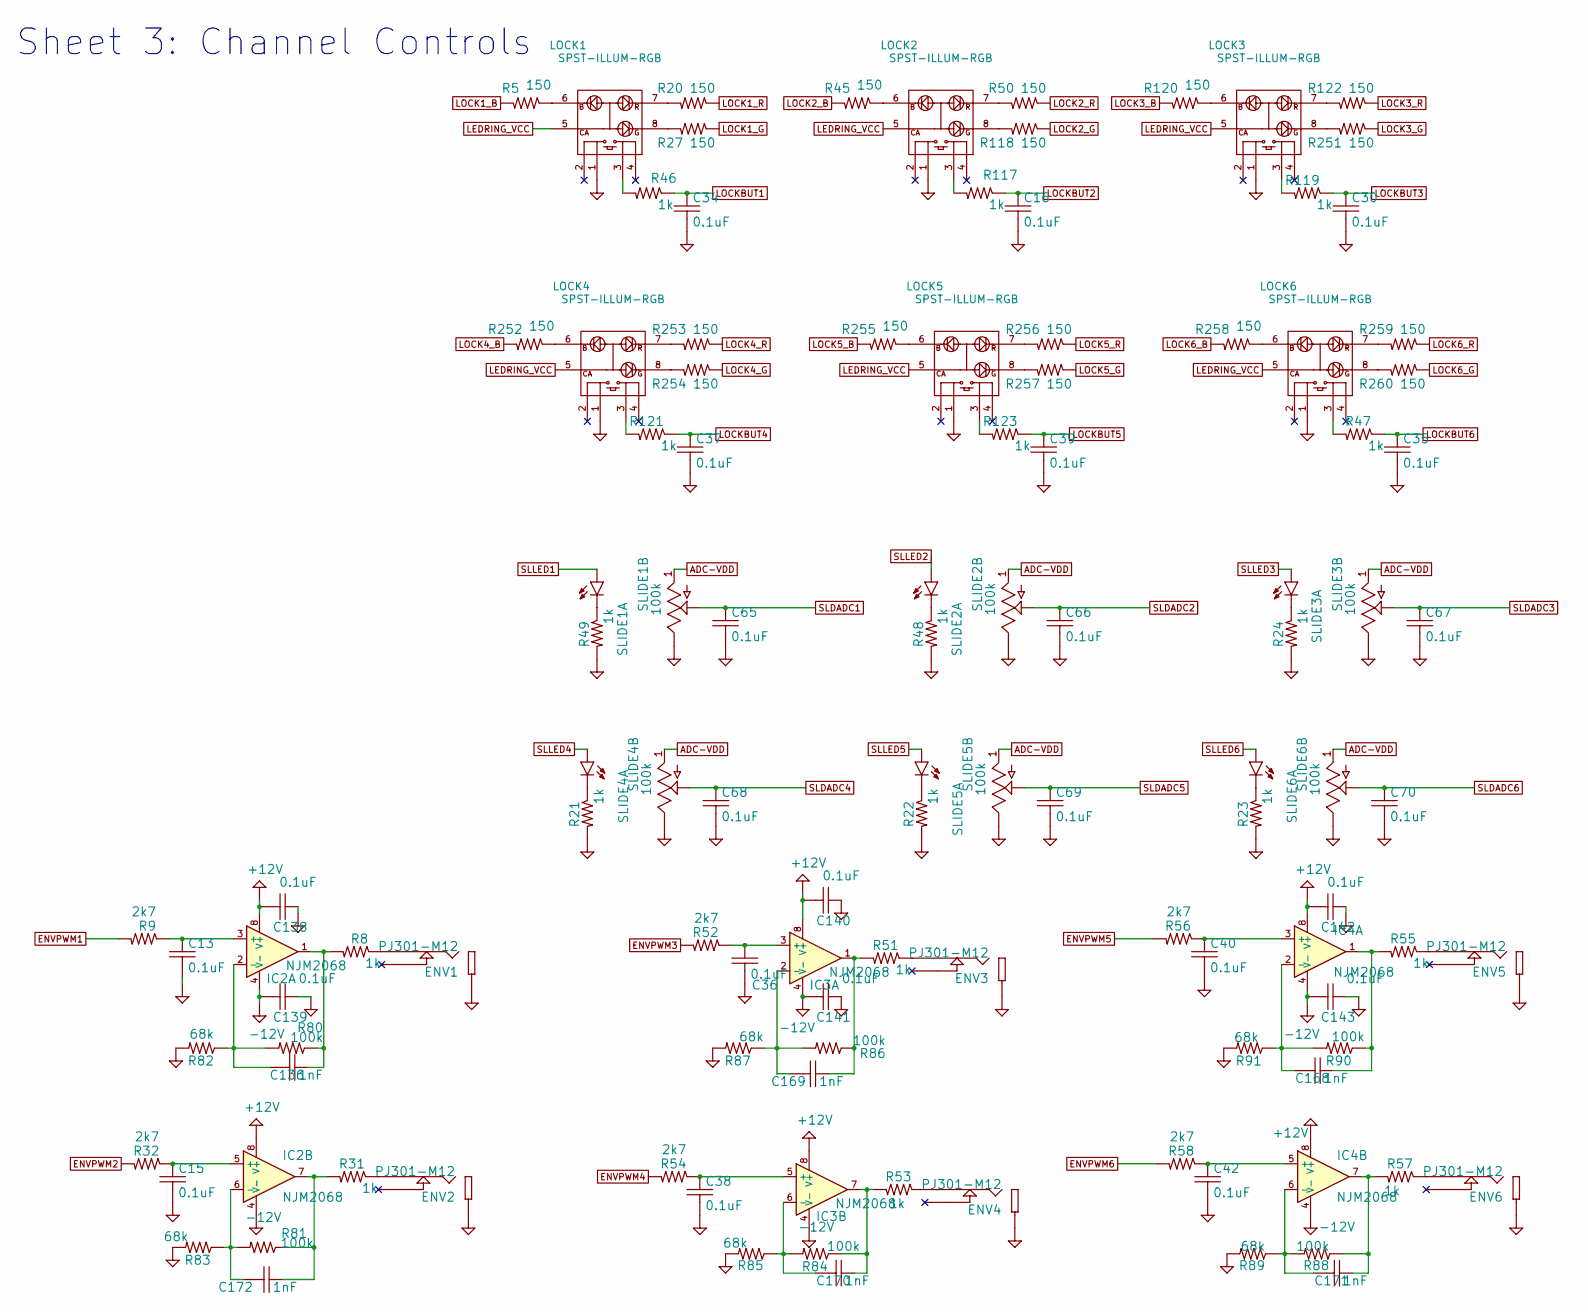
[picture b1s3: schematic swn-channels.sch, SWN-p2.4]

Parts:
C13, C15, C16, C30, C34, C35, C36, C37, C38, C39, C40, C42, C65, C66, C67, C68, C69, C70, C138, C139, C140, C141, C142, C143: 0.1uF; C0603
C136, C168, C169, C170, C171, C172: 1nF; C0603
ENV1, ENV2, ENV3, ENV4, ENV5, ENV6: PJ301-M12; PJ301M-12
IC2, IC3, IC4: NJM2068; TSSOP-8_4.4x3mm_Pitch0.65mm
LOCK1, LOCK2, LOCK3, LOCK4, LOCK5, LOCK6: SPST-ILLUM-RGB; RGB-SPST-LED-TC002
R5, R20, R27, R45, R50, R118, R120, R122, R251, R252, R253, R254, R255, R256, R257, R258, R259, R260: 150; R0603
R8, R21, R22, R23, R24, R31, R46, R47, R48, R49, R51, R53, R55, R57, R117, R119, R121, R123: 1k; R0603
R9, R32, R52, R54, R56, R58: 2k7; R0603
R80, R81, R84, R86, R88, R90: 100k; R0603
R82, R83, R85, R87, R89, R91: 68k; R0603
SLIDE1, SLIDE2, SLIDE3, SLIDE4, SLIDE5, SLIDE6: 100k; POT-SLIDER-LED-ALPHA-RA2045F-20

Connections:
+12V: C138.2, C140.2, C142.2, IC2.8 (V+), IC3.8 (V+), IC4.8 (V+); also elsewhere on the board
-12V: C139.2, C141.2, C143.2, IC2.4 (V-), IC3.4 (V-), IC4.4 (V-); also elsewhere on the board
ADC-VDD: SLIDE1.P1 (1), SLIDE2.P1 (1), SLIDE3.P1 (1), SLIDE4.P1 (1), SLIDE5.P1 (1), SLIDE6.P1 (1); also elsewhere on the board
ENVPWM1: R9.2; also elsewhere on the board
ENVPWM2: R32.2; also elsewhere on the board
ENVPWM3: R52.2; also elsewhere on the board
ENVPWM4: R54.2; also elsewhere on the board
ENVPWM5: R56.2; also elsewhere on the board
ENVPWM6: R58.2; also elsewhere on the board
LEDRING_VCC: LOCK1.5 (CA), LOCK2.5 (CA), LOCK3.5 (CA), LOCK4.5 (CA), LOCK5.5 (CA), LOCK6.5 (CA); also elsewhere on the board
LOCK1_B: R5.2; also elsewhere on the board
LOCK1_G: R27.1; also elsewhere on the board
LOCK1_R: R20.1; also elsewhere on the board
LOCK2_B: R45.2; also elsewhere on the board
LOCK2_G: R118.1; also elsewhere on the board
LOCK2_R: R50.1; also elsewhere on the board
LOCK3_B: R120.2; also elsewhere on the board
LOCK3_G: R251.1; also elsewhere on the board
LOCK3_R: R122.1; also elsewhere on the board
LOCK4_B: R252.2; also elsewhere on the board
LOCK4_G: R254.1; also elsewhere on the board
LOCK4_R: R253.1; also elsewhere on the board
LOCK5_B: R255.2; also elsewhere on the board
LOCK5_G: R257.1; also elsewhere on the board
LOCK5_R: R256.1; also elsewhere on the board
LOCK6_B: R258.2; also elsewhere on the board
LOCK6_G: R260.1; also elsewhere on the board
LOCK6_R: R259.1; also elsewhere on the board
LOCKBUT1: C34.1, R46.1; also elsewhere on the board
LOCKBUT2: C16.1, R117.1; also elsewhere on the board
LOCKBUT3: C30.1, R119.1; also elsewhere on the board
LOCKBUT4: C37.1, R121.1; also elsewhere on the board
LOCKBUT5: C39.1, R123.1; also elsewhere on the board
LOCKBUT6: C35.1, R47.1; also elsewhere on the board
unnamed: C13.1, IC2.3 (+), R9.1
unnamed: C15.1, IC2.5 (+), R32.1
unnamed: C36.1, IC3.3 (+), R52.1
unnamed: C38.1, IC3.5 (+), R54.1
unnamed: C40.1, IC4.3 (+), R56.1
unnamed: C42.1, IC4.5 (+), R58.1
unnamed: C136.1, IC2.1, R8.2, R80.1
unnamed: C136.2, IC2.2 (-), R80.2, R82.1
unnamed: C168.1, IC4.1, R55.2, R90.1
unnamed: C168.2, IC4.2 (-), R90.2, R91.1
unnamed: C169.1, IC3.1, R51.2, R86.1
unnamed: C169.2, IC3.2 (-), R86.2, R87.1
unnamed: C170.1, IC3.7, R53.2, R84.1
unnamed: C170.2, IC3.6 (-), R84.2, R85.1
unnamed: C171.1, IC4.7, R57.2, R88.1
unnamed: C171.2, IC4.6 (-), R88.2, R89.1
unnamed: C172.1, IC2.7, R31.2, R81.1
unnamed: C172.2, IC2.6 (-), R81.2, R83.1
unnamed: ENV1.1 (TIP), R8.1
unnamed: ENV2.1 (TIP), R31.1
unnamed: ENV3.1 (TIP), R51.1
unnamed: ENV4.1 (TIP), R53.1
unnamed: ENV5.1 (TIP), R55.1
unnamed: ENV6.1 (TIP), R57.1
unnamed: LOCK1.3 (DOWN-A), R46.2
unnamed: LOCK1.6 (G), R5.1
unnamed: LOCK1.7 (R), R20.2
unnamed: LOCK1.8 (B), R27.2
unnamed: LOCK2.3 (DOWN-A), R117.2
unnamed: LOCK2.6 (G), R45.1
unnamed: LOCK2.7 (R), R50.2
unnamed: LOCK2.8 (B), R118.2
unnamed: LOCK3.3 (DOWN-A), R119.2
unnamed: LOCK3.6 (G), R120.1
unnamed: LOCK3.7 (R), R122.2
unnamed: LOCK3.8 (B), R251.2
unnamed: LOCK4.3 (DOWN-A), R121.2
unnamed: LOCK4.6 (G), R252.1
unnamed: LOCK4.7 (R), R253.2
unnamed: LOCK4.8 (B), R254.2
unnamed: LOCK5.3 (DOWN-A), R123.2
unnamed: LOCK5.6 (G), R255.1
unnamed: LOCK5.7 (R), R256.2
unnamed: LOCK5.8 (B), R257.2
unnamed: LOCK6.3 (DOWN-A), R47.2
unnamed: LOCK6.6 (G), R258.1
unnamed: LOCK6.7 (R), R259.2
unnamed: LOCK6.8 (B), R260.2
unnamed: R21.1, SLIDE4.LEDC (C)
unnamed: R22.1, SLIDE5.LEDC (C)
unnamed: R23.1, SLIDE6.LEDC (C)
unnamed: R24.1, SLIDE3.LEDC (C)
unnamed: R48.1, SLIDE2.LEDC (C)
unnamed: R49.1, SLIDE1.LEDC (C)
SLDADC1: C65.1, SLIDE1.P2 (2); also elsewhere on the board
SLDADC2: C66.1, SLIDE2.P2 (2); also elsewhere on the board
SLDADC3: C67.1, SLIDE3.P2 (2); also elsewhere on the board
SLDADC4: C68.1, SLIDE4.P2 (2); also elsewhere on the board
SLDADC5: C69.1, SLIDE5.P2 (2); also elsewhere on the board
SLDADC6: C70.1, SLIDE6.P2 (2); also elsewhere on the board
SLLED1: SLIDE1.LEDA (A); also elsewhere on the board
SLLED2: SLIDE2.LEDA (A); also elsewhere on the board
SLLED3: SLIDE3.LEDA (A); also elsewhere on the board
SLLED4: SLIDE4.LEDA (A); also elsewhere on the board
SLLED5: SLIDE5.LEDA (A); also elsewhere on the board
SLLED6: SLIDE6.LEDA (A); also elsewhere on the board

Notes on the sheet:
Sheet 3: Channel Controls
